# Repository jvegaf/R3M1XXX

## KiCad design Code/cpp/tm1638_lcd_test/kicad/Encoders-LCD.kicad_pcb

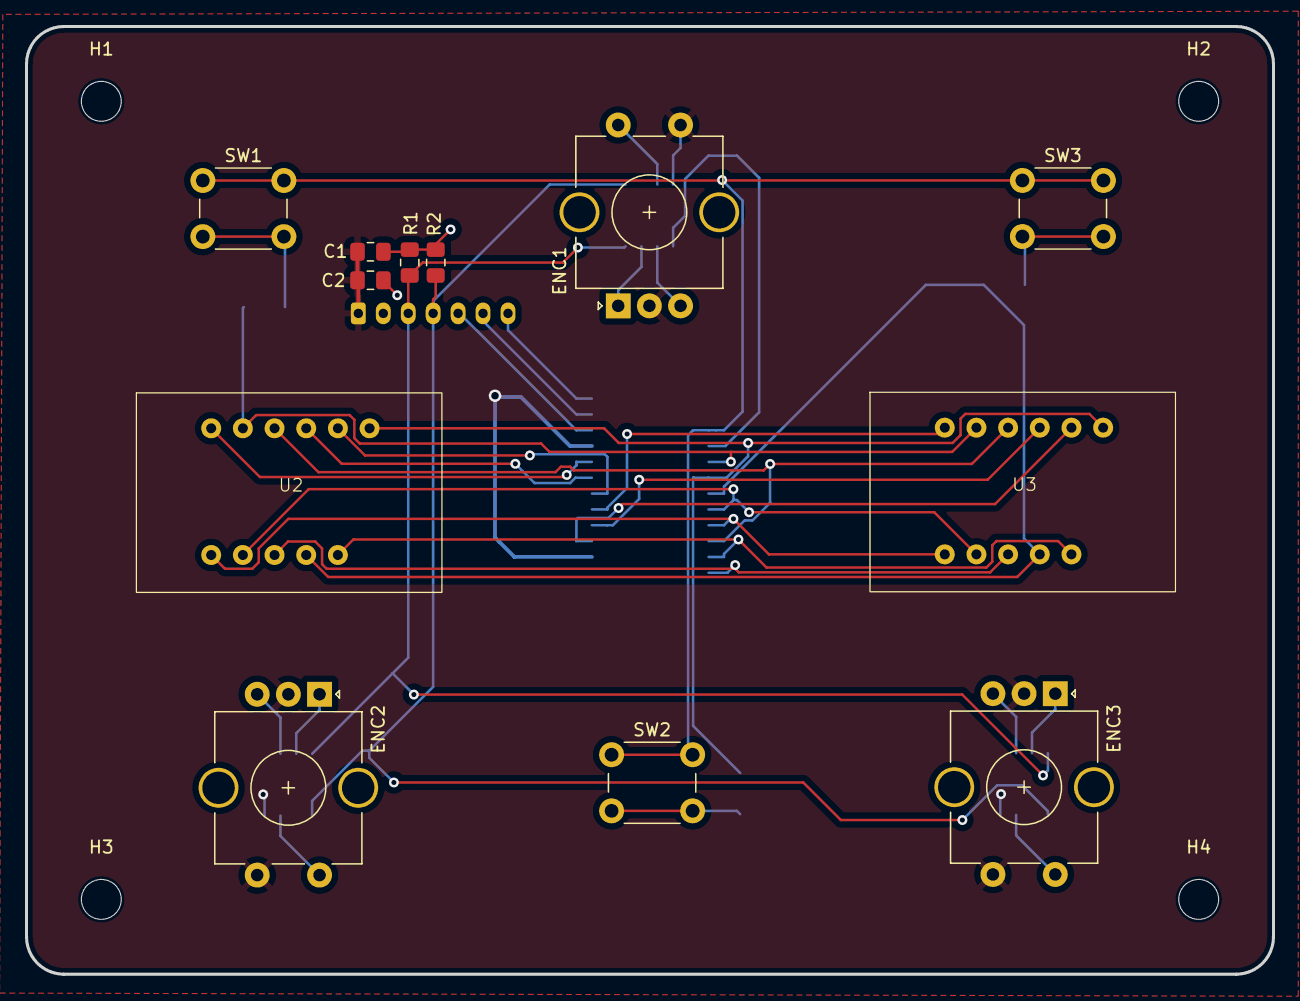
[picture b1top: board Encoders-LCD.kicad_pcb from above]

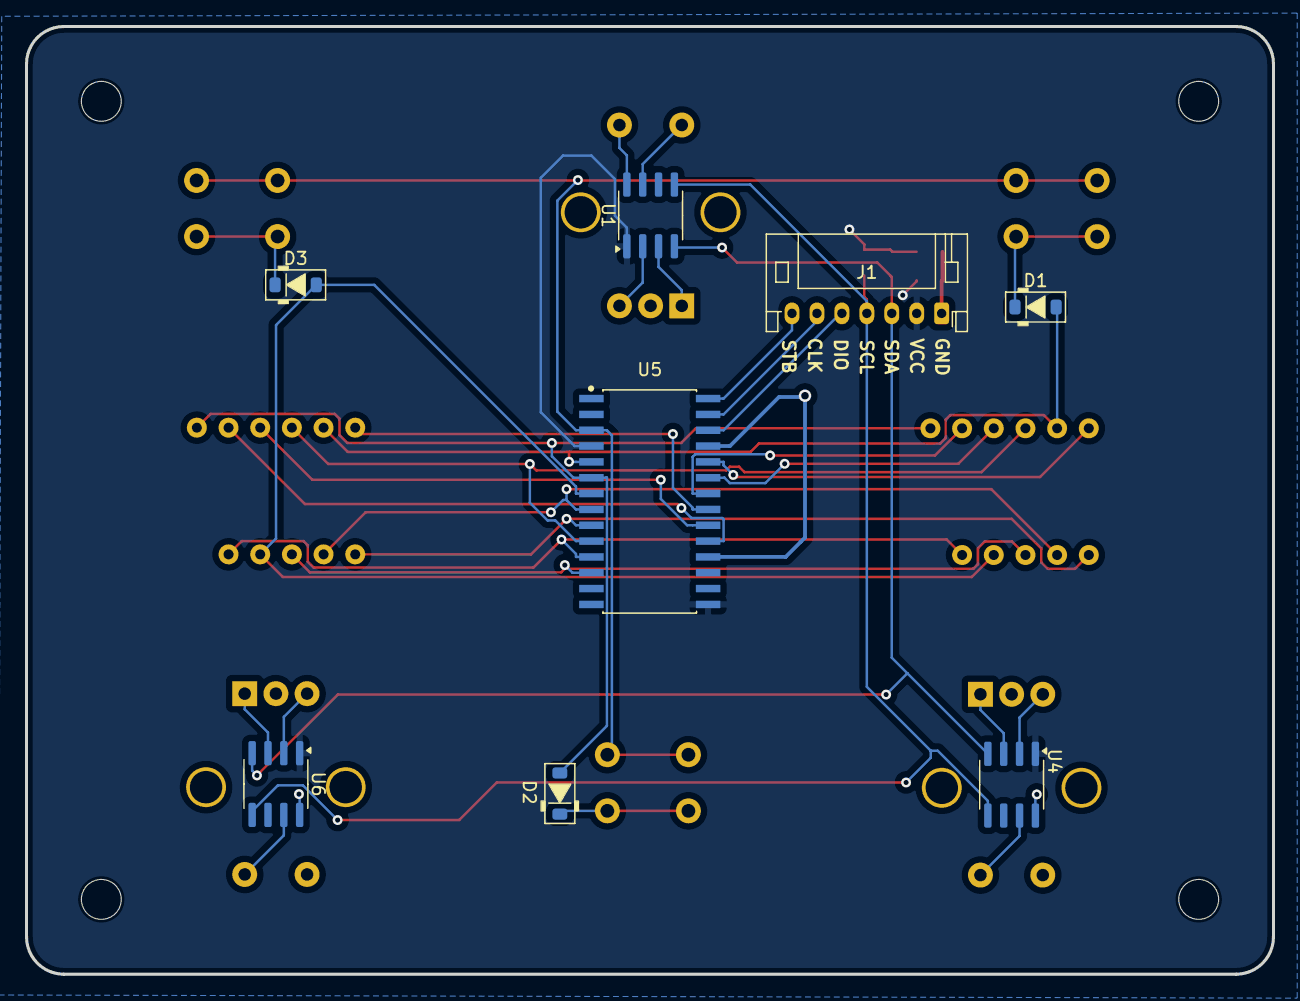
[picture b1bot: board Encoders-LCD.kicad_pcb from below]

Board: 2 copper layers, 100.0 x 76.0 mm, 24 parts (8 on the bottom side), 34 nets.

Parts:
C1: 100nF; C_0805_2012Metric_Pad1.18x1.45mm_HandSolder
C2: 10uF; C_0805_2012Metric_Pad1.18x1.45mm_HandSolder
D1, D2, D3: 4148; D_SOD-123
ENC1, ENC2, ENC3: Encoder; self-RotaryEncoder_Alps_EC11E-Switch_Vertical_H20mm_Circula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
H1, H2, H3, H4: MountingHole_M3; MountingHole_3.2mm_M3
J1: Conn_01x07; JST_PH_S7B-PH-K_1x07_P2.00mm_Horizontal
R1, R2: 10K; C_0805_2012Metric_Pad1.18x1.45mm_HandSolder
SW1: SW_LEFT; SW_PUSH_6mm_H4.3mm
SW2: SW_SHIFT; SW_PUSH_6mm_H4.3mm
SW3: SW_RIGHT; SW_PUSH_6mm_H4.3mm
U1, U4, U6: ATtiny412-SS; SOIC-8_3.9x4.9mm_P1.27mm
U2, U3: 3631AS
U5: TM1638; SOIC127P1041X265-28N

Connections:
/A1: ENC1.A, U1.3 (PA7)
/A2: ENC2.A, U4.3 (PA7)
/A3: ENC3.A, U6.3 (PA7)
/B1: ENC1.B, U1.2 (PA6)
/B2: ENC2.B, U4.2 (PA6)
/B3: ENC3.B, U6.2 (PA6)
/CLK: J1.6, U5.27 (CLK)
/DIO: J1.5, U5.26 (DIO)
/GR1: U2.12 (DIG1), U5.24 (GRID1)
/GR2: U2.9 (DIG2), U5.23 (GRID2)
/GR3: U2.8 (DIG3), U5.22 (GRID3)
/GR4: U3.12 (DIG1), U5.21 (GRID4)
/GR5: U3.9 (DIG2), U5.20 (GRID5)
/GR6: U3.8 (DIG3), U5.19 (GRID6)
/K3: SW1.1, SW2.1, SW3.1, U5.3 (K3)
/SCL: J1.4, R2.2, U1.5 (PA2), U4.5 (PA2), U6.5 (PA2)
/SDA: J1.3, R1.2, U1.4 (PA1), U4.4 (PA1), U6.4 (PA1)
/SEG1: D1.2 (A), U2.11 (A), U3.11 (A), U5.5 (SEG/KS1)
/SEG2: D2.2 (A), U2.7 (B), U3.7 (B), U5.6 (SEG/KS2)
/SEG3: D3.2 (A), U2.4 (C), U3.4 (C), U5.7 (SEG/KS3)
/SEG4: U2.2 (D), U3.2 (D), U5.8 (SEG/KS4)
/SEG5: U2.1 (E), U3.1 (E), U5.9 (SEG/KS5)
/SEG6: U2.10 (F), U3.10 (F), U5.10 (SEG/KS6)
/SEG7: U2.5 (G), U3.5 (G), U5.11 (SEG/KS7)
/SEG8: U2.3 (DP), U3.3 (DP), U5.12 (SEG/KS8)
/STB: J1.7, U5.28 (~STB)
/SW1: ENC1.S2, U1.7 (PA3)
/SW2: ENC2.S2, U4.7 (PA3)
/SW3: ENC3.S2, U6.7 (PA3)
GND: C1.2, C2.2, ENC1.C, ENC1.S1, ENC2.C, ENC2.S1, ENC3.C, ENC3.S1, J1.1, U1.8 (GND), U4.8 (GND), U5.18 (GND), U5.25 (GND), U6.8 (GND)
unnamed: D1.1 (K), SW1.2
unnamed: D2.1 (K), SW2.2
unnamed: D3.1 (K), SW3.2
VCC: C1.1, C2.1, J1.2, R1.1, R2.1, U1.1 (VCC), U4.1 (VCC), U5.4 (VCC), U5.15 (VDD), U6.1 (VCC)

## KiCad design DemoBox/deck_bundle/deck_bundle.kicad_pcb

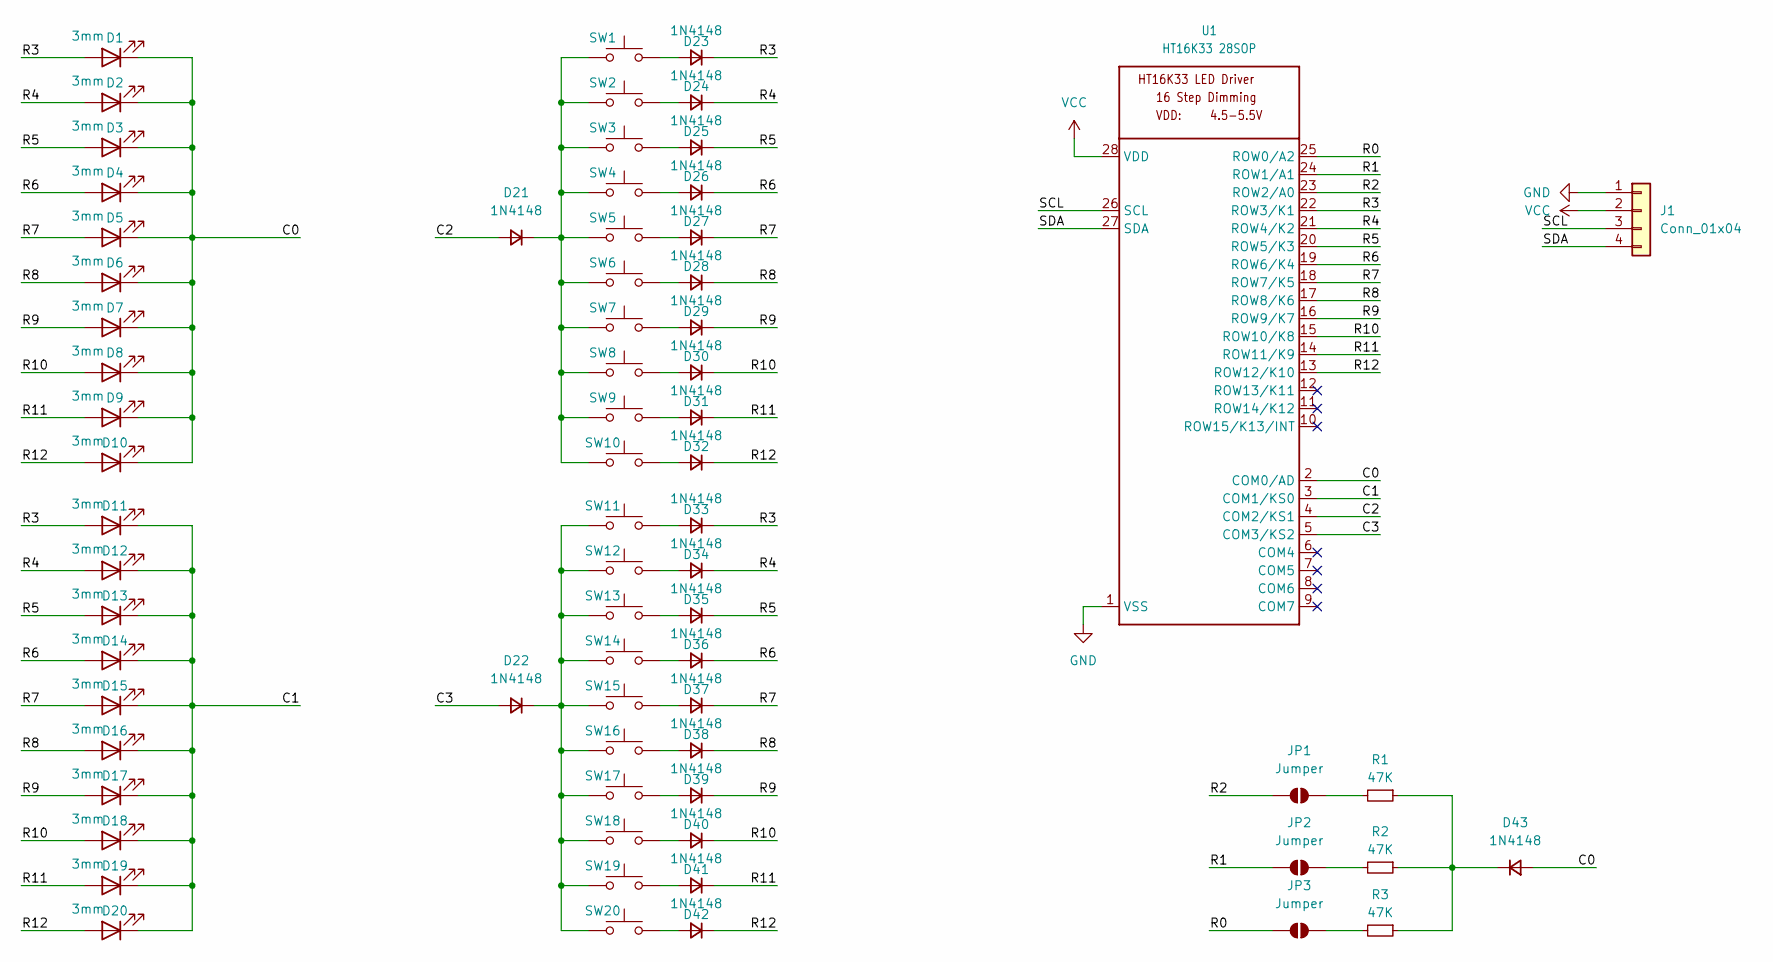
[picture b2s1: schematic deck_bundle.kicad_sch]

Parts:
D1, D2, D3, D4, D5, D6, D7, D8, D9, D10, D11, D12, D13, D14, D15, D16, D17, D18, D19, D20: 3mm; LED_D3.0mm
D21, D22, D23, D24, D25, D26, D27, D28, D29, D30, D31, D32, D33, D34, D35, D36, D37, D38, D39, D40, D41, D42, D43: 1N4148; D_SOD-123
J1: Conn_01x04; Molex_KK-254_AE-6410-04A_1x04_P2.54mm_Vertical
JP1, JP2, JP3: Jumper; SolderJumper-2_P1.3mm_Open_RoundedPad1.0x1.5mm
R1, R2, R3: 47K; R_0805_2012Metric_Pad1.15x1.40mm_HandSolder
SW1, SW2, SW3, SW4, SW5, SW6, SW7, SW8, SW9, SW10, SW11, SW12, SW13, SW14, SW15, SW16, SW17, SW18, SW19, SW20: SW_Push; SW_PUSH_6mm_H5mm
U1: HT16K33 28SOP; SOP-28_8.4x18.16mm_P1.27mm

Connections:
/C0: D1.1 (K), D2.1 (K), D3.1 (K), D4.1 (K), D5.1 (K), D6.1 (K), D7.1 (K), D8.1 (K), D9.1 (K), D10.1 (K), D43.2 (A), U1.2 (COM0/AD)
/C1: D11.1 (K), D12.1 (K), D13.1 (K), D14.1 (K), D15.1 (K), D16.1 (K), D17.1 (K), D18.1 (K), D19.1 (K), D20.1 (K), U1.3 (COM1/KS0)
/C2: D21.2 (A), U1.4 (COM2/KS1)
/C3: D22.2 (A), U1.5 (COM3/KS2)
/R0: JP3.1 (A), U1.25 (ROW0/A2)
/R1: JP2.1 (A), U1.24 (ROW1/A1)
/R2: JP1.1 (A), U1.23 (ROW2/A0)
/R3: D1.2 (A), D11.2 (A), D23.1 (K), D33.1 (K), U1.22 (ROW3/K1)
/R4: D2.2 (A), D12.2 (A), D24.1 (K), D34.1 (K), U1.21 (ROW4/K2)
/R5: D3.2 (A), D13.2 (A), D25.1 (K), D35.1 (K), U1.20 (ROW5/K3)
/R6: D4.2 (A), D14.2 (A), D26.1 (K), D36.1 (K), U1.19 (ROW6/K4)
/R7: D5.2 (A), D15.2 (A), D27.1 (K), D37.1 (K), U1.18 (ROW7/K5)
/R8: D6.2 (A), D16.2 (A), D28.1 (K), D38.1 (K), U1.17 (ROW8/K6)
/R9: D7.2 (A), D17.2 (A), D29.1 (K), D39.1 (K), U1.16 (ROW9/K7)
/R10: D8.2 (A), D18.2 (A), D30.1 (K), D40.1 (K), U1.15 (ROW10/K8)
/R11: D9.2 (A), D19.2 (A), D31.1 (K), D41.1 (K), U1.14 (ROW11/K9)
/R12: D10.2 (A), D20.2 (A), D32.1 (K), D42.1 (K), U1.13 (ROW12/K10)
/SCL: J1.3, U1.26 (SCL)
/SDA: J1.4, U1.27 (SDA)
GND: J1.1, U1.1 (VSS)
unnamed: D21.1 (K), SW1.1, SW2.1, SW3.1, SW4.1, SW5.1, SW6.1, SW7.1, SW8.1, SW9.1, SW10.1
unnamed: D22.1 (K), SW11.1, SW12.1, SW13.1, SW14.1, SW15.1, SW16.1, SW17.1, SW18.1, SW19.1, SW20.1
unnamed: D23.2 (A), SW1.2
unnamed: D24.2 (A), SW2.2
unnamed: D25.2 (A), SW3.2
unnamed: D26.2 (A), SW4.2
unnamed: D27.2 (A), SW5.2
unnamed: D28.2 (A), SW6.2
unnamed: D29.2 (A), SW7.2
unnamed: D30.2 (A), SW8.2
unnamed: D31.2 (A), SW9.2
unnamed: D32.2 (A), SW10.2
unnamed: D33.2 (A), SW11.2
unnamed: D34.2 (A), SW12.2
unnamed: D35.2 (A), SW13.2
unnamed: D36.2 (A), SW14.2
unnamed: D37.2 (A), SW15.2
unnamed: D38.2 (A), SW16.2
unnamed: D39.2 (A), SW17.2
unnamed: D40.2 (A), SW18.2
unnamed: D41.2 (A), SW19.2
unnamed: D42.2 (A), SW20.2
unnamed: D43.1 (K), R1.1, R2.1, R3.1
unnamed: JP1.2 (B), R1.2
unnamed: JP2.2 (B), R2.2
unnamed: JP3.2 (B), R3.2
VCC: J1.2, U1.28 (VDD)

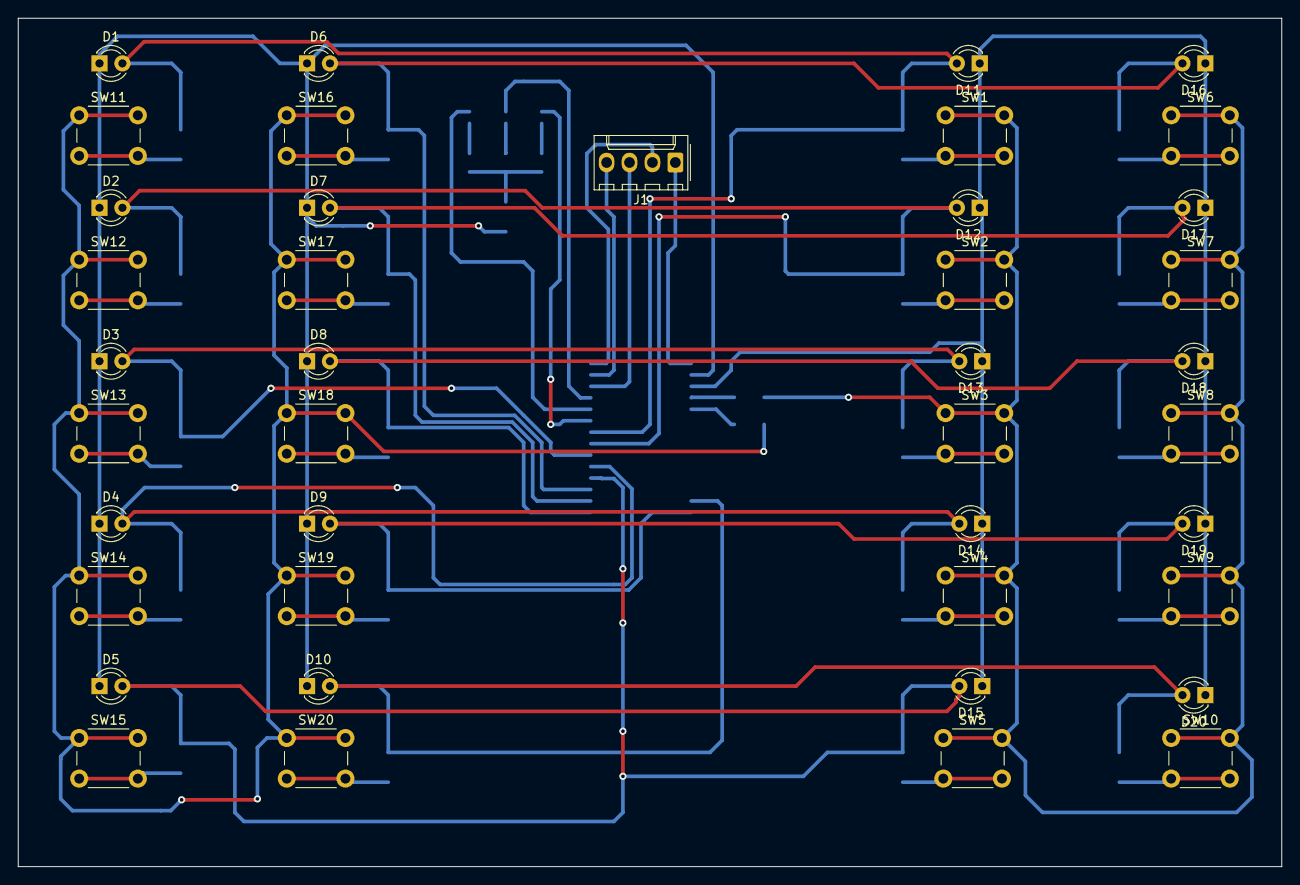
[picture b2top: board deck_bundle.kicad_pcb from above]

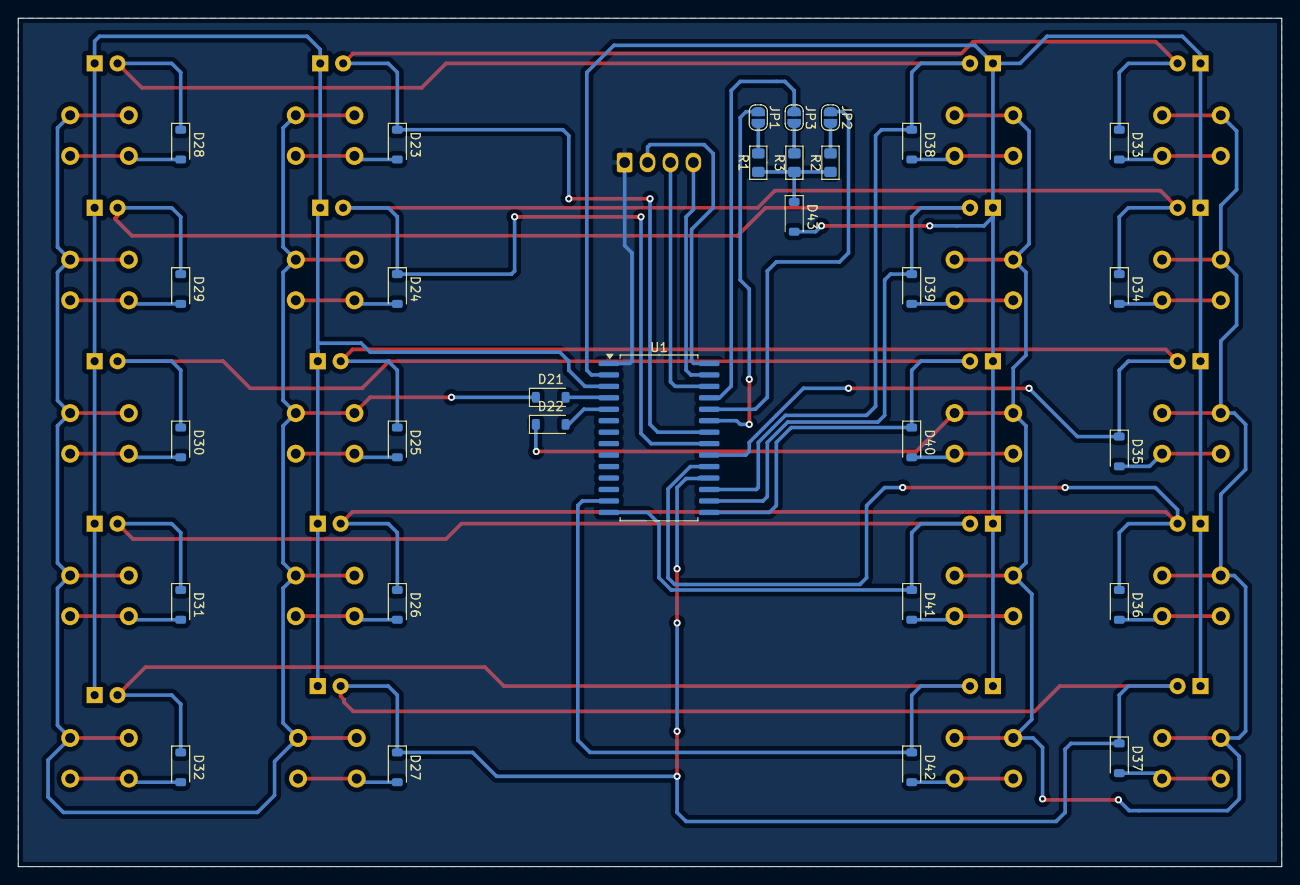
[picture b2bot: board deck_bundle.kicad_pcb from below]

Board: 2 copper layers, 140.0 x 94.0 mm, 71 parts (30 on the bottom side), 47 nets.

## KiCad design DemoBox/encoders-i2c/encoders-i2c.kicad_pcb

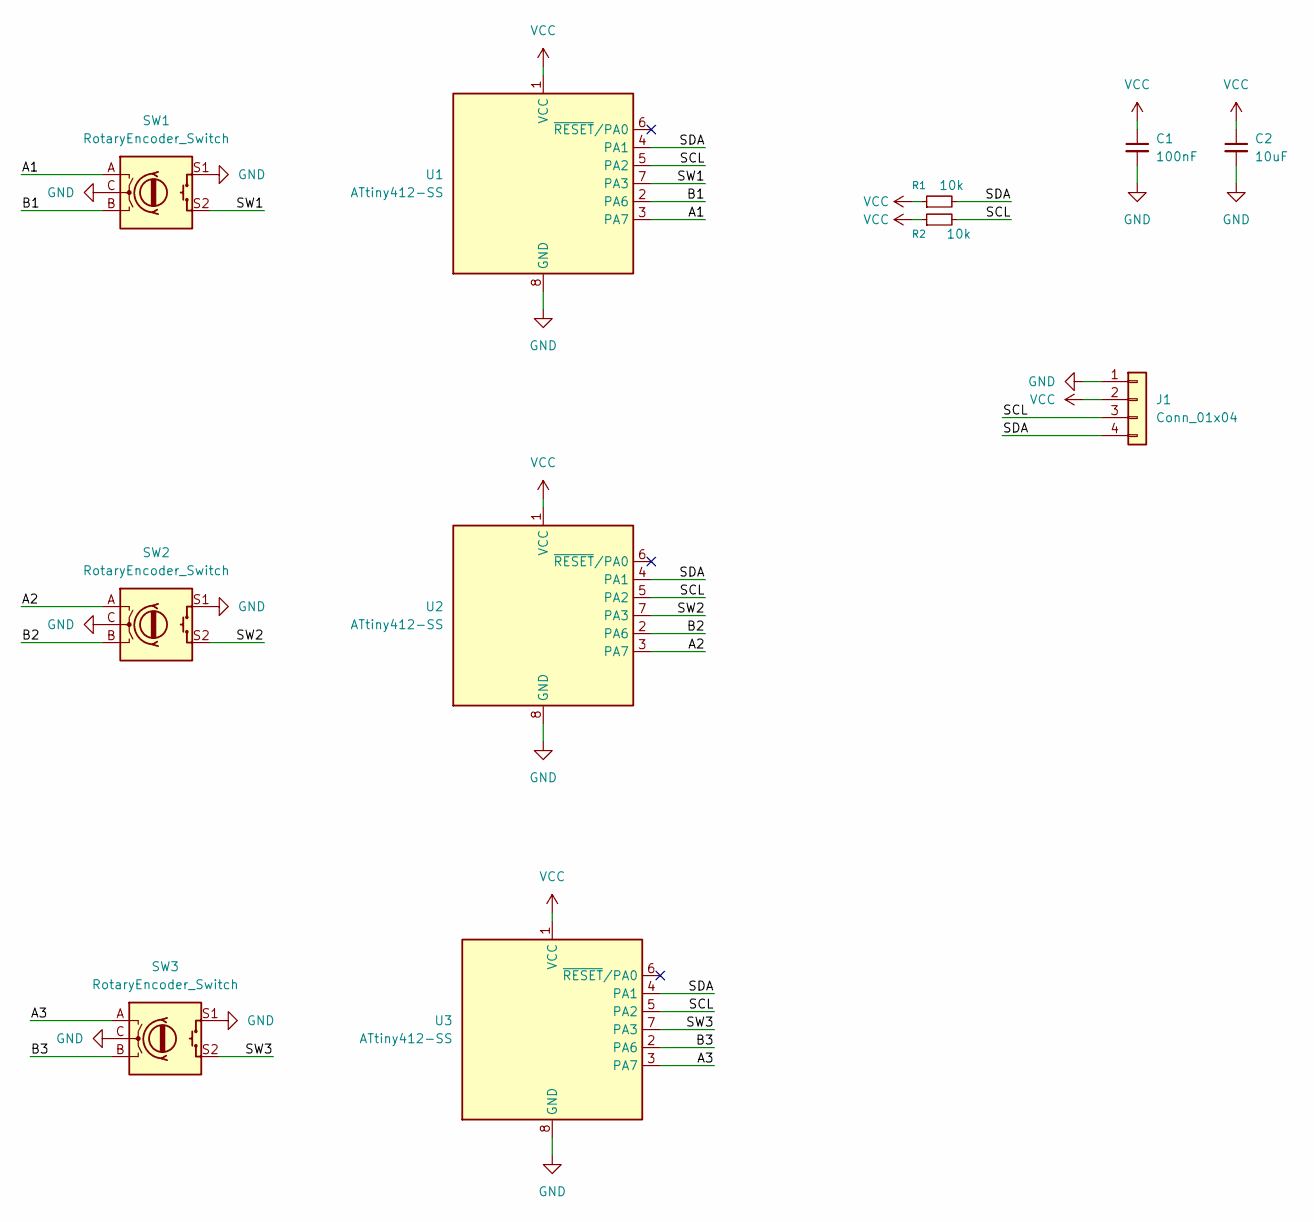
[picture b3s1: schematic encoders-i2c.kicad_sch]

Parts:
C1: 100nF; C_0805_2012Metric_Pad1.18x1.45mm_HandSolder
C2: 10uF; C_0805_2012Metric_Pad1.18x1.45mm_HandSolder
J1: Conn_01x04; Molex_KK-254_AE-6410-04A_1x04_P2.54mm_Vertical
R1, R2: 10k; R_0805_2012Metric_Pad1.20x1.40mm_HandSolder
SW1, SW2, SW3: RotaryEncoder_Switch; RotaryEncoder_Alps_EC11E-Switch_Vertical_H20mm_CircularMoun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
U1, U2, U3: ATtiny412-SS; SOIC-8_3.9x4.9mm_P1.27mm

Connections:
/A1: SW1.A, U1.3 (PA7)
/A2: SW2.A, U2.3 (PA7)
/A3: SW3.A, U3.3 (PA7)
/B1: SW1.B, U1.2 (PA6)
/B2: SW2.B, U2.2 (PA6)
/B3: SW3.B, U3.2 (PA6)
/SCL: J1.3, R2.2, U1.5 (PA2), U2.5 (PA2), U3.5 (PA2)
/SDA: J1.4, R1.2, U1.4 (PA1), U2.4 (PA1), U3.4 (PA1)
/SW1: SW1.S2, U1.7 (PA3)
/SW2: SW2.S2, U2.7 (PA3)
/SW3: SW3.S2, U3.7 (PA3)
GND: C1.2, C2.2, J1.1, SW1.C, SW1.S1, SW2.C, SW2.S1, SW3.C, SW3.S1, U1.8 (GND), U2.8 (GND), U3.8 (GND)
VCC: C1.1, C2.1, J1.2, R1.1, R2.1, U1.1 (VCC), U2.1 (VCC), U3.1 (VCC)

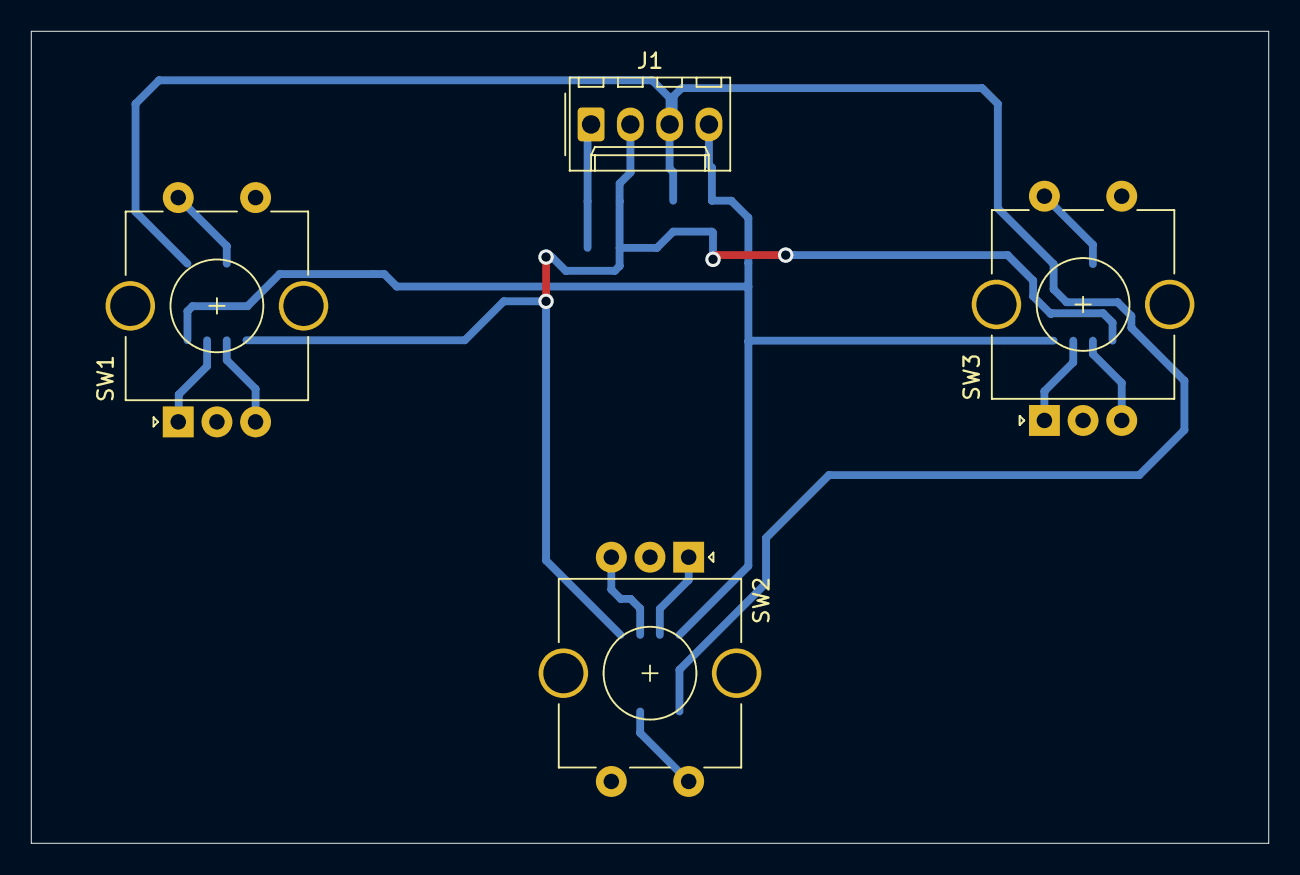
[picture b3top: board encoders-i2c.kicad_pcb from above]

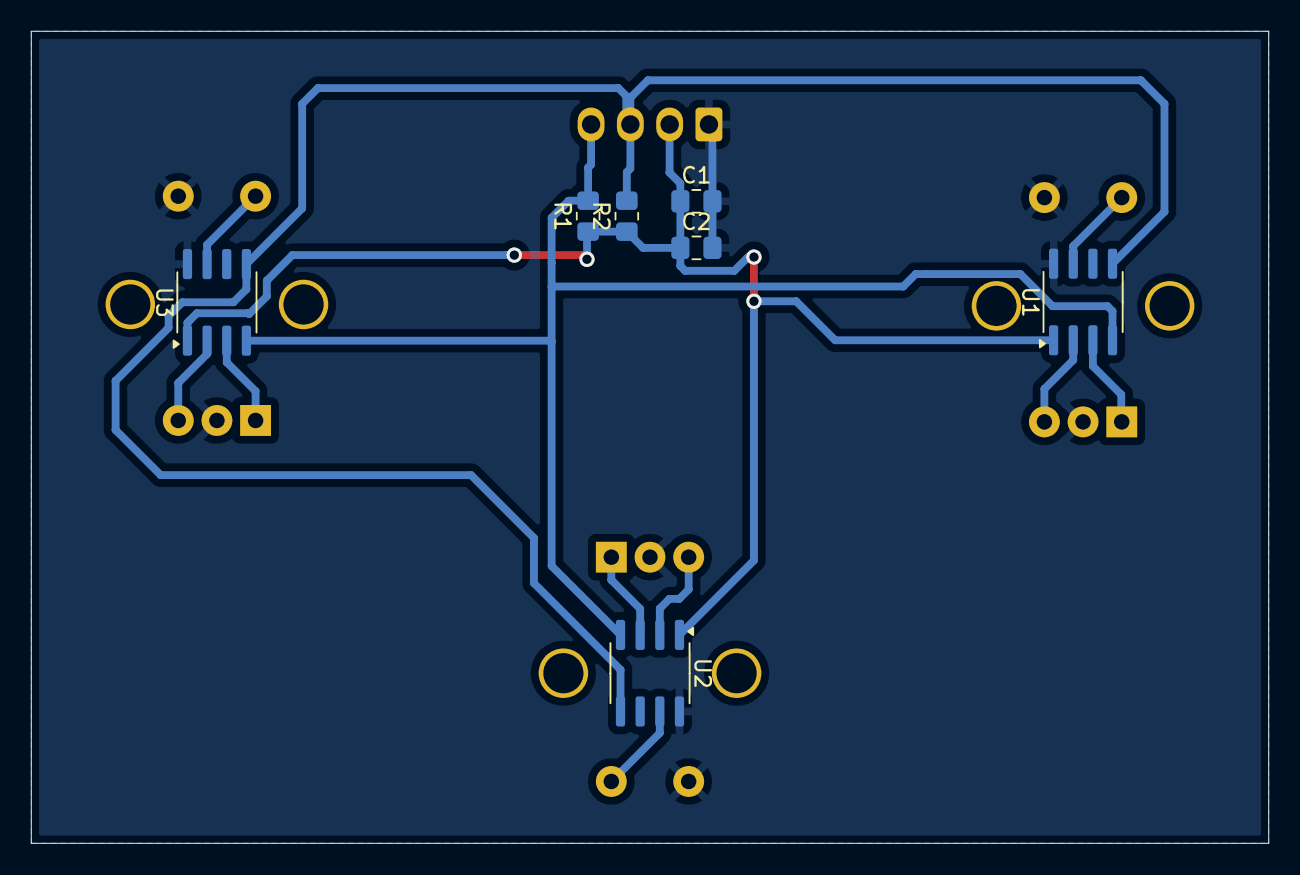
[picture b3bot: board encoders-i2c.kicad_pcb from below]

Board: 2 copper layers, 80.0 x 52.5 mm, 11 parts (7 on the bottom side), 13 nets.

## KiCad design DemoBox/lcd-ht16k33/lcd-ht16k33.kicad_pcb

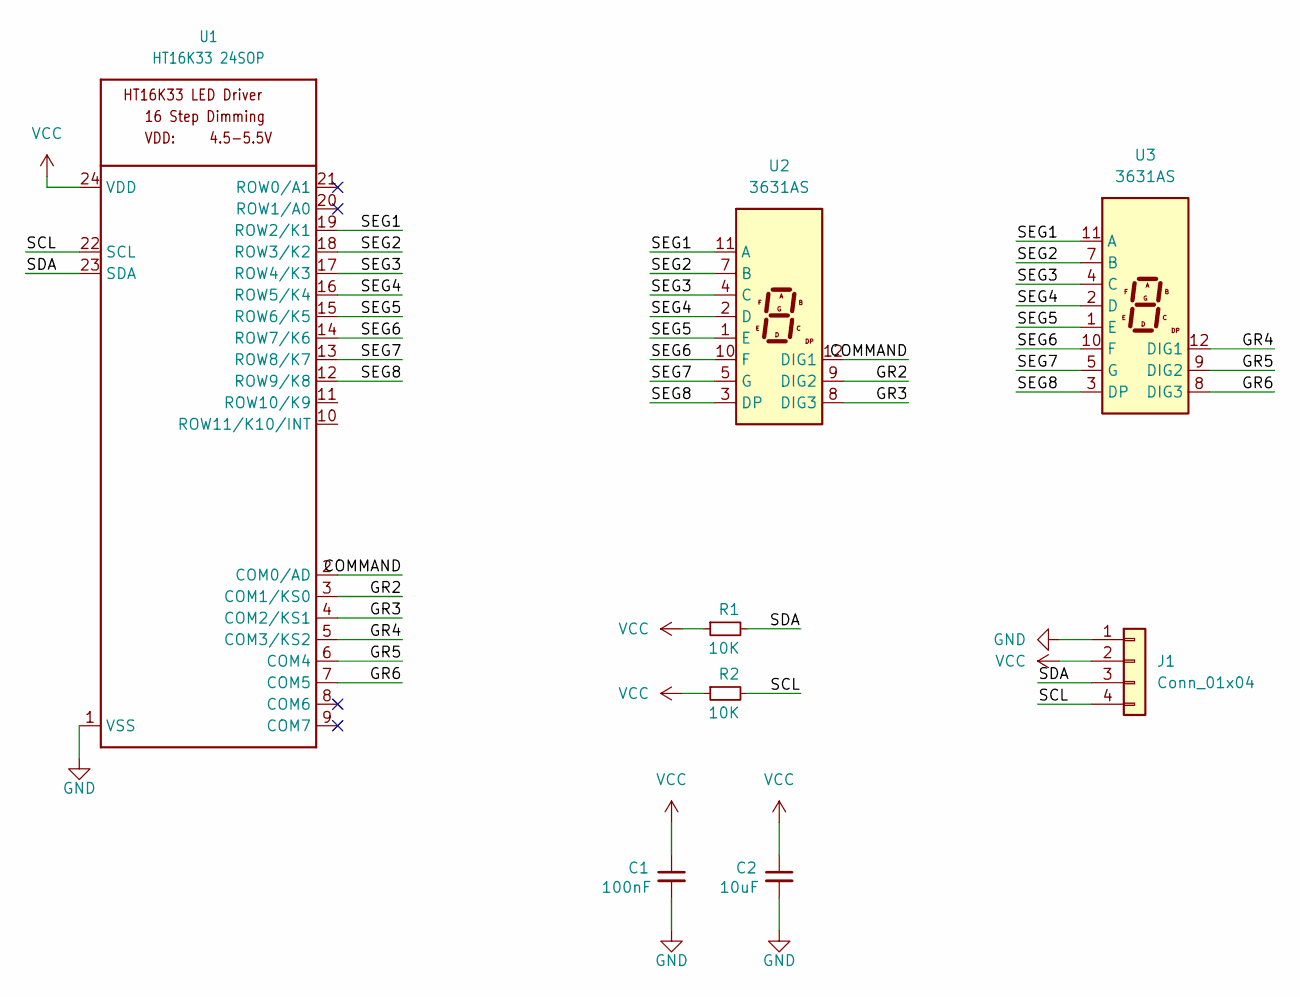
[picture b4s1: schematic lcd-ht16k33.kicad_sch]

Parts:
C1: 100nF; C_1206_3216Metric_Pad1.33x1.80mm_HandSolder
C2: 10uF; C_0805_2012Metric_Pad1.18x1.45mm_HandSolder
J1: Conn_01x04; Molex_KK-254_AE-6410-04A_1x04_P2.54mm_Vertical
R1, R2: 10K; C_0805_2012Metric_Pad1.18x1.45mm_HandSolder
U1: HT16K33 24SOP; SOP-24_7.5x15.4mm_P1.27mm
U2, U3: 3631AS

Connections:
/COMMAND: U1.2 (COM0/AD), U2.12 (DIG1)
/GR2: U1.3 (COM1/KS0), U2.9 (DIG2)
/GR3: U1.4 (COM2/KS1), U2.8 (DIG3)
/GR4: U1.5 (COM3/KS2), U3.12 (DIG1)
/GR5: U1.6 (COM4), U3.9 (DIG2)
/GR6: U1.7 (COM5), U3.8 (DIG3)
/SCL: J1.4, R2.2, U1.22 (SCL)
/SDA: J1.3, R1.2, U1.23 (SDA)
/SEG1: U1.19 (ROW2/K1), U2.11 (A), U3.11 (A)
/SEG2: U1.18 (ROW3/K2), U2.7 (B), U3.7 (B)
/SEG3: U1.17 (ROW4/K3), U2.4 (C), U3.4 (C)
/SEG4: U1.16 (ROW5/K4), U2.2 (D), U3.2 (D)
/SEG5: U1.15 (ROW6/K5), U2.1 (E), U3.1 (E)
/SEG6: U1.14 (ROW7/K6), U2.10 (F), U3.10 (F)
/SEG7: U1.13 (ROW8/K7), U2.5 (G), U3.5 (G)
/SEG8: U1.12 (ROW9/K8), U2.3 (DP), U3.3 (DP)
GND: C1.2, C2.2, J1.1, U1.1 (VSS)
VCC: C1.1, C2.1, J1.2, R1.1, R2.1, U1.24 (VDD)

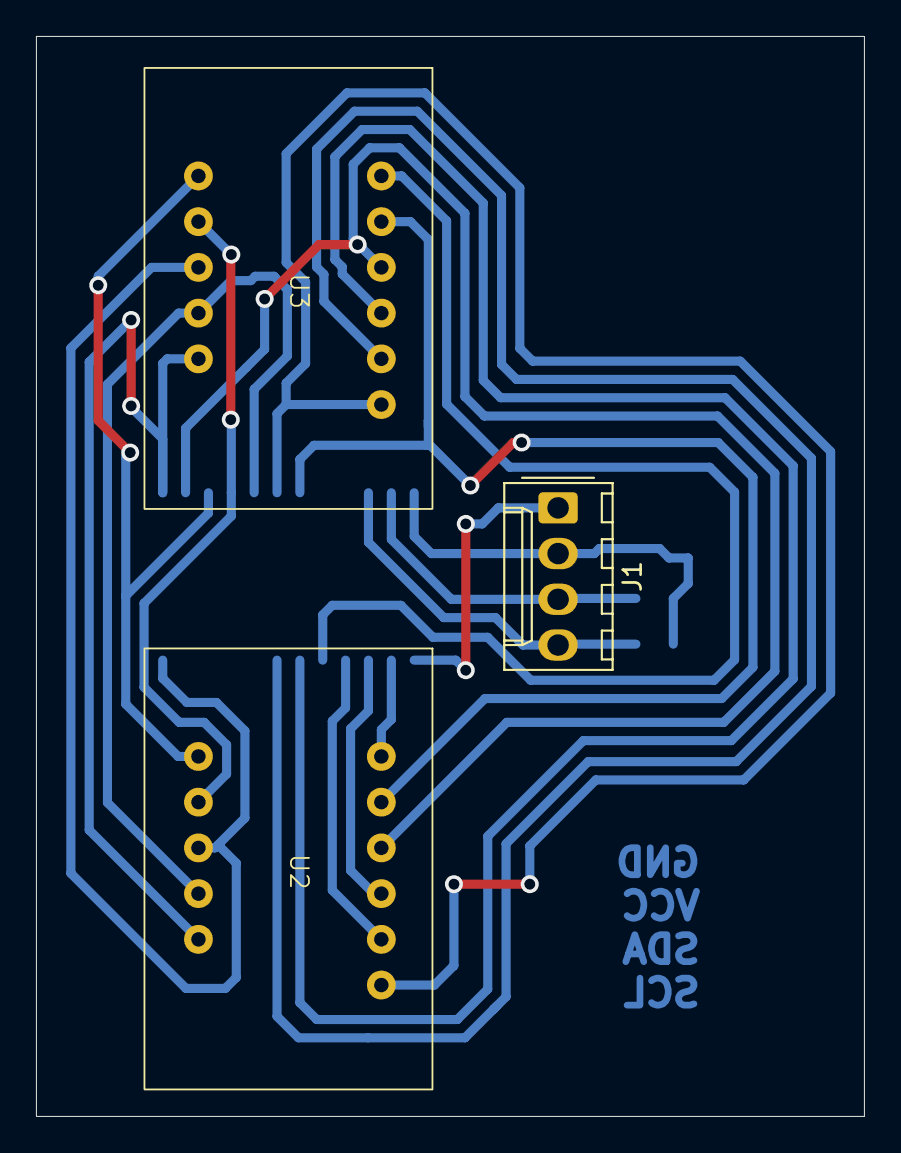
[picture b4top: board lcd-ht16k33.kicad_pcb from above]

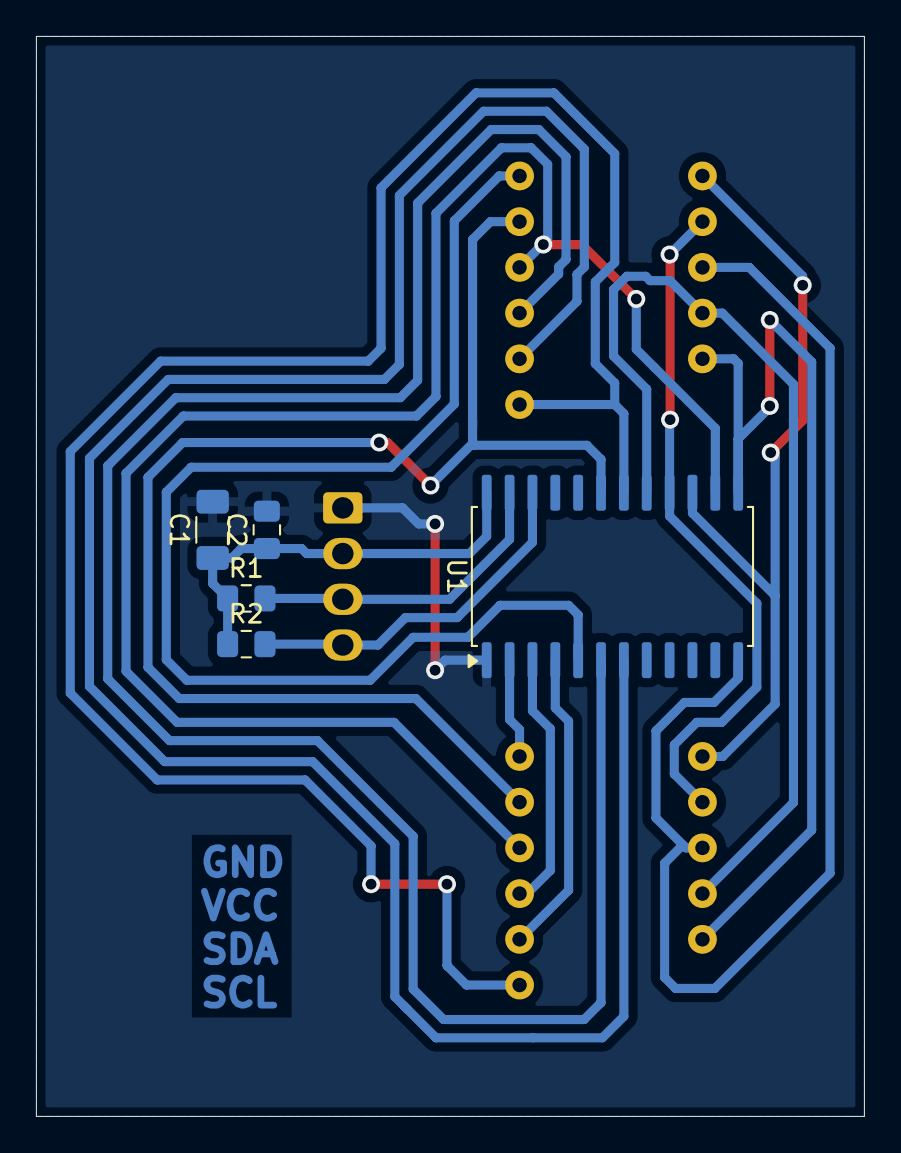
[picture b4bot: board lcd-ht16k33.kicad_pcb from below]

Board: 2 copper layers, 46.0 x 60.0 mm, 8 parts (5 on the bottom side), 18 nets.

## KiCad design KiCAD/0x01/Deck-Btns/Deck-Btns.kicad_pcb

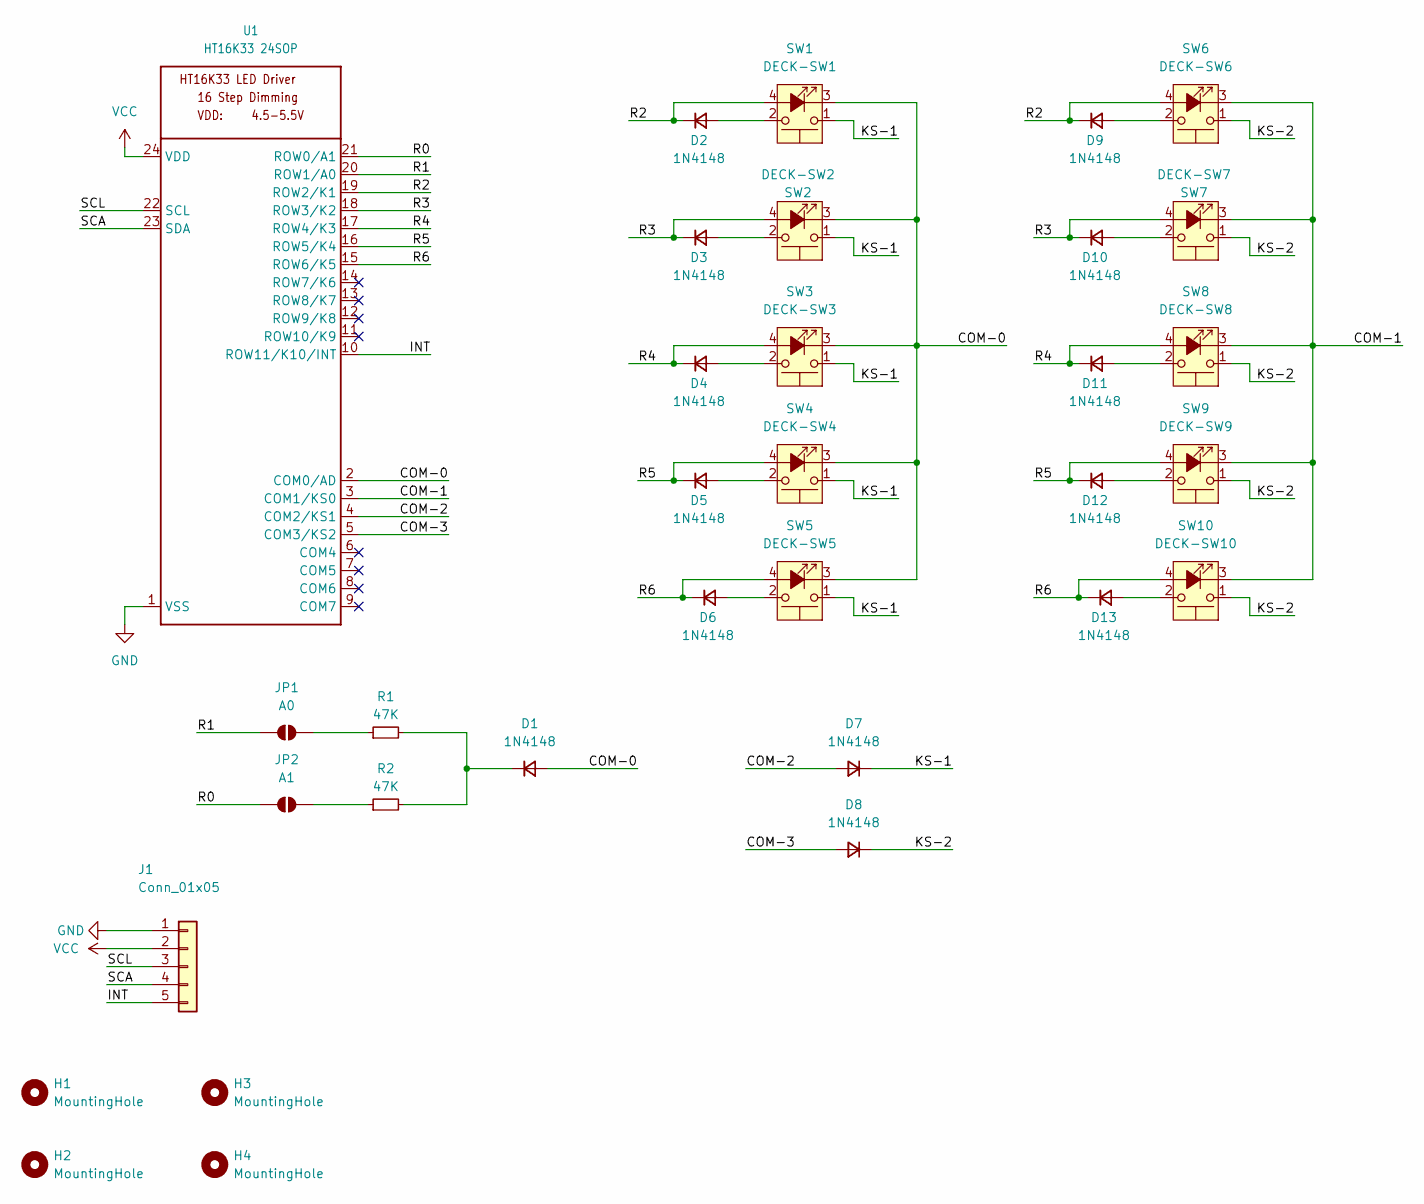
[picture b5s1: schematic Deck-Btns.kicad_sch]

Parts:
D1, D2, D3, D4, D5, D6, D7, D8, D9, D10, D11, D12, D13: 1N4148; D_SOD-123
H1, H2, H3, H4: MountingHole; MountingHole_3.2mm_M3
J1: Conn_01x05; Hirose_DF13-05P-1.25DSA_1x05_P1.25mm_Vertical
JP1: A0; SolderJumper-2_P1.3mm_Open_RoundedPad1.0x1.5mm
JP2: A1; SolderJumper-2_P1.3mm_Open_RoundedPad1.0x1.5mm
R1, R2: 47K; R_0805_2012Metric_Pad1.20x1.40mm_HandSolder
SW1: DECK-SW1; led switch
SW2: DECK-SW2; led switch
SW3: DECK-SW3; led switch
SW4: DECK-SW4; led switch
SW5: DECK-SW5; led switch
SW6: DECK-SW6; led switch
SW7: DECK-SW7; led switch
SW8: DECK-SW8; led switch
SW9: DECK-SW9; led switch
SW10: DECK-SW10; led switch
U1: HT16K33 24SOP; SSOP-24_5.3x8.2mm_P0.65mm

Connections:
/COM-0: D1.2 (A), SW1.3 (K), SW2.3 (K), SW3.3 (K), SW4.3 (K), SW5.3 (K), U1.2 (COM0/AD)
/COM-1: SW6.3 (K), SW7.3 (K), SW8.3 (K), SW9.3 (K), SW10.3 (K), U1.3 (COM1/KS0)
/COM-2: D7.2 (A), U1.4 (COM2/KS1)
/COM-3: D8.2 (A), U1.5 (COM3/KS2)
/INT: J1.5, U1.10 (ROW11/K10/INT)
/KS-1: D7.1 (K), SW1.1, SW2.1, SW3.1, SW4.1, SW5.1
/KS-2: D8.1 (K), SW6.1, SW7.1, SW8.1, SW9.1, SW10.1
/R0: JP2.1 (A), U1.21 (ROW0/A1)
/R1: JP1.1 (A), U1.20 (ROW1/A0)
/R2: D2.1 (K), D9.1 (K), SW1.4 (A), SW6.4 (A), U1.19 (ROW2/K1)
/R3: D3.1 (K), D10.1 (K), SW2.4 (A), SW7.4 (A), U1.18 (ROW3/K2)
/R4: D4.1 (K), D11.1 (K), SW3.4 (A), SW8.4 (A), U1.17 (ROW4/K3)
/R5: D5.1 (K), D12.1 (K), SW4.4 (A), SW9.4 (A), U1.16 (ROW5/K4)
/R6: D6.1 (K), D13.1 (K), SW5.4 (A), SW10.4 (A), U1.15 (ROW6/K5)
/SCA: J1.4, U1.23 (SDA)
/SCL: J1.3, U1.22 (SCL)
GND: J1.1, U1.1 (VSS)
unnamed: D1.1 (K), R1.2, R2.2
unnamed: D2.2 (A), SW1.2
unnamed: D3.2 (A), SW2.2
unnamed: D4.2 (A), SW3.2
unnamed: D5.2 (A), SW4.2
unnamed: D6.2 (A), SW5.2
unnamed: D9.2 (A), SW6.2
unnamed: D10.2 (A), SW7.2
unnamed: D11.2 (A), SW8.2
unnamed: D12.2 (A), SW9.2
unnamed: D13.2 (A), SW10.2
unnamed: JP1.2 (B), R1.1
unnamed: JP2.2 (B), R2.1
VCC: J1.2, U1.24 (VDD)

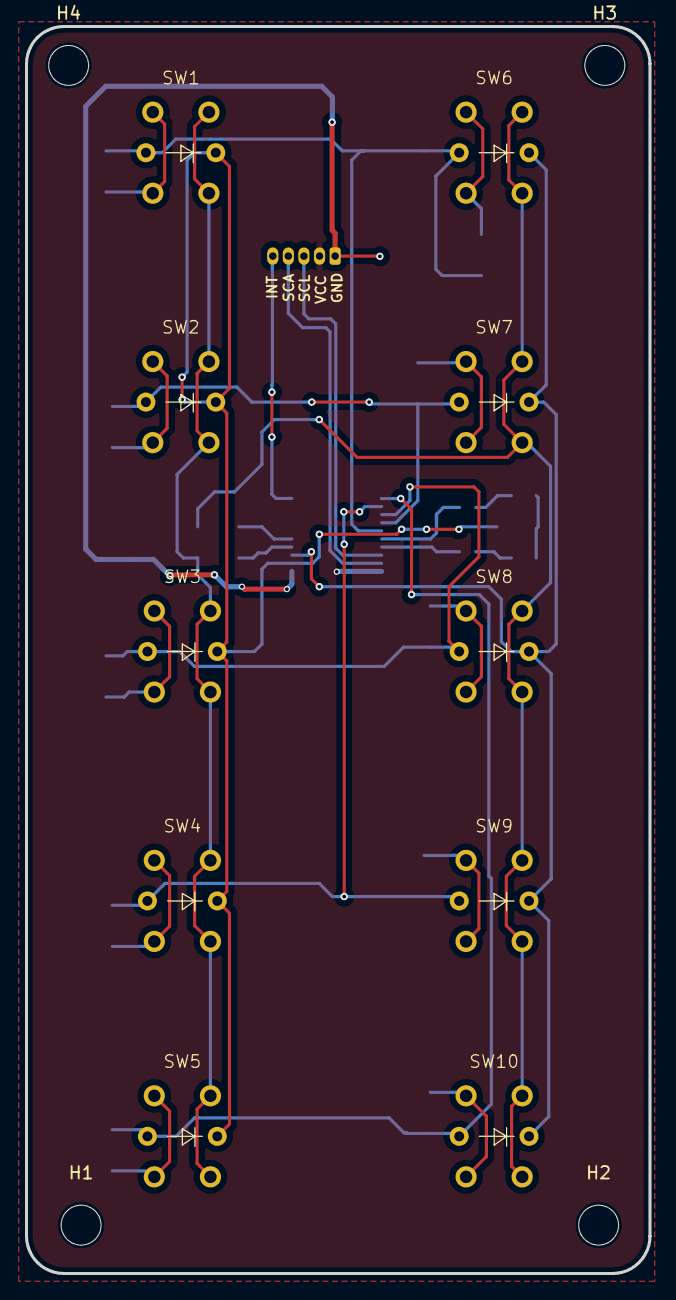
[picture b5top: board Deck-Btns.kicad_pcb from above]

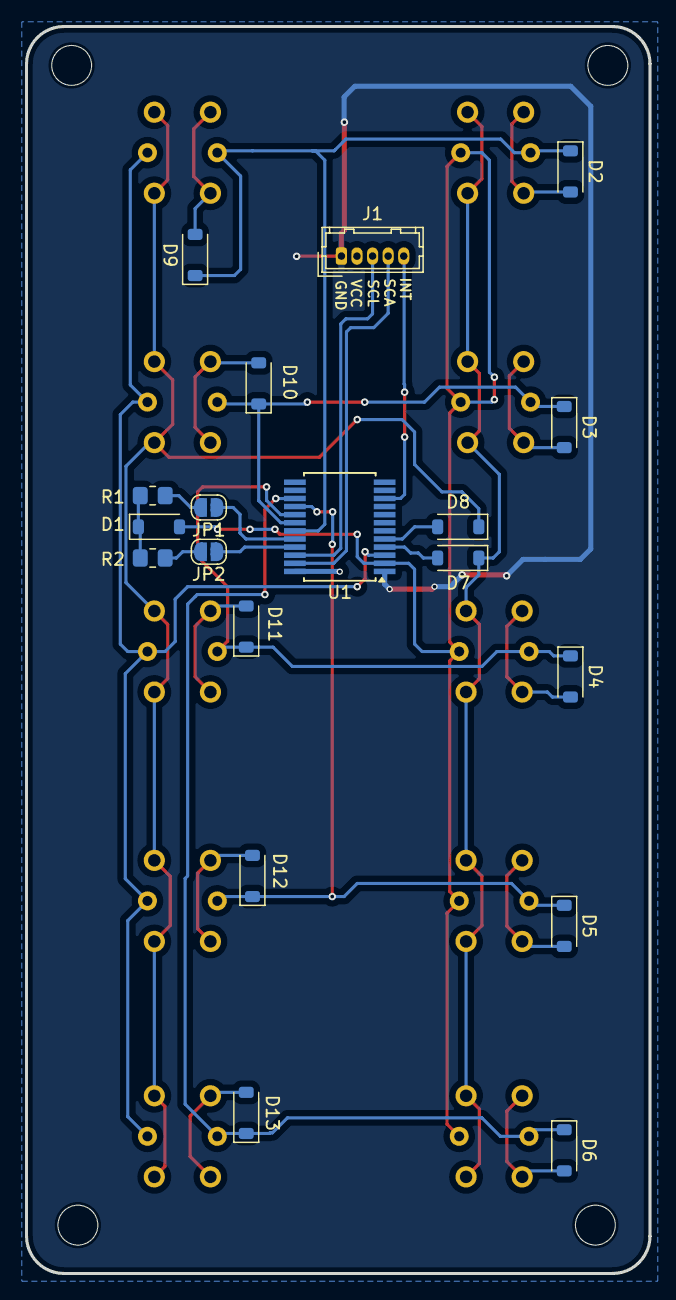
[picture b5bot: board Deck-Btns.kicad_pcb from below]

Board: 2 copper layers, 50.0 x 100.0 mm, 33 parts (19 on the bottom side), 31 nets.
